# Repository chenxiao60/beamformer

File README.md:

beamformer
==============

Source files for senior tech project

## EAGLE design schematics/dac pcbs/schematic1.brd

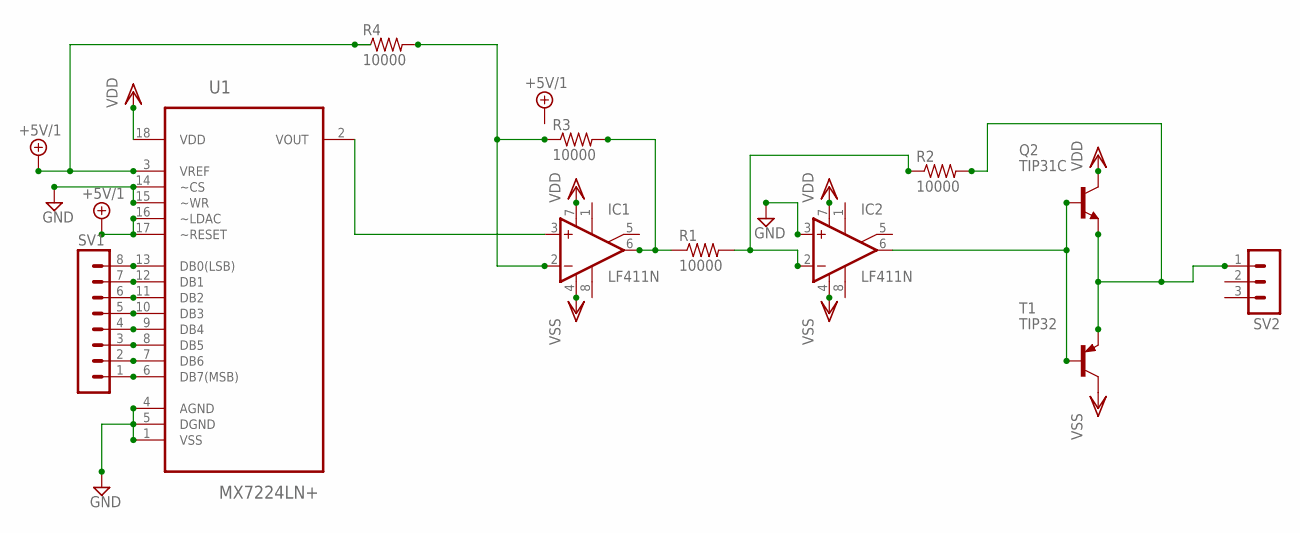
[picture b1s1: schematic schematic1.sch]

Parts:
IC1, IC2: LF411N; DIL08
Q2: TIP31C; TO220
R1, R2, R3, R4: 10000; 0204/7
SV1: MA08-1W
SV2: MA03-1
T1: TIP32; TO220
U1: MX7224LN+; DIP254P762X457-18

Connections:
+5V/1: R4.1, U1.3 (VREF), U1.16 (~LDAC), U1.17 (~RESET)
GND: IC2.3 (+IN), U1.1 (VSS), U1.4 (AGND), U1.5 (DGND), U1.14 (~CS), U1.15 (~WR)
unnamed: IC1.6 (OUT), R1.1, R3.2
unnamed: IC2.2 (-IN), R1.2, R2.1
unnamed: IC2.6 (OUT), Q2.1 (B), T1.1 (B)
unnamed: IC1.3 (+IN), U1.2 (VOUT)
unnamed: IC1.2 (-IN), R3.1, R4.2
unnamed: SV1.1, U1.6 (DB7(MSB))
unnamed: SV1.2, U1.7 (DB6)
unnamed: SV1.3, U1.8 (DB5)
unnamed: SV1.4, U1.9 (DB4)
unnamed: SV1.5, U1.10 (DB3)
unnamed: SV1.6, U1.11 (DB2)
unnamed: SV1.7, U1.12 (DB1)
unnamed: SV1.8, U1.13 (DB0(LSB))
O0: Q2.3 (E), R2.2, SV2.1, T1.3 (E)
VDD: IC1.7 (V+), IC2.7 (V+), Q2.2 (C), U1.18 (VDD)
VSS: IC1.4 (V-), IC2.4 (V-), T1.2 (C)

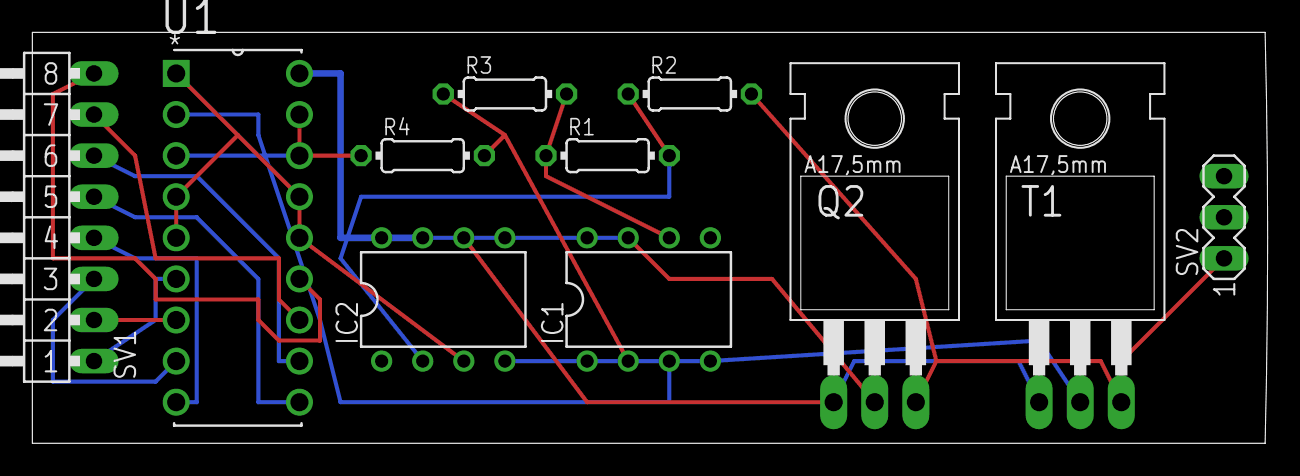
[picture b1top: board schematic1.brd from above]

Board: 2 copper layers, 76.4 x 25.4 mm, 11 parts (0 on the bottom side), 18 nets.

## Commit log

2013-12-10 initial version
2013-12-10 cleaned up naming
2013-12-10 fixed testbench
2013-12-10 working simulation
2013-12-10 new idea for timing
2013-12-10 channel select timing working
2013-12-10 ds_store changed
2013-12-12 initial dac timing fix
2013-12-18 edited ucf file
2014-01-07 configured testbech
2014-01-07 caught bug in input method
2014-01-07 testbench edits
2014-01-09 ldac timing fix
2014-01-10 ldac refix
2014-01-16 fixed overflow issues
2014-02-12 used combinatorial logic
2014-02-26 changed delays
2014-02-26 changed comment
2014-02-26 new method for processing
2014-02-26 fixed counter labeling
2014-02-27 changed simulation method
2014-02-27 cleared data bus buffers on each us clock
2014-02-27 new method to clear registers
2014-02-27 added high impedence output
2014-02-27 deleted high impedence output
2014-02-27 changed to quiessent point output
2014-02-27 changed sample period
2014-02-27 edited out clearing registers
2014-03-07 sample period update
2014-03-10 initial farfield commit
2014-03-10 wrote far-field delays
2014-03-11 loading registers fix
2014-03-11 fixed sample_edges
2014-03-11 fixed clock issues
2014-03-11 fixed clock division issue
2014-03-11 fixed counter timing
2014-03-11 far-field working
2014-03-11 far-field synthesizes
2014-03-12 all outputs working
2014-03-13 changed sample timing
2014-03-13 updated pin names & changed sampling method
2014-03-14 new output method
2014-03-14 fixed sample_period sensitivity list issue
2014-03-14 synchronous resets
2014-03-14 updated delays to generics
2014-03-14 new counter method
2014-03-14 fixed sample updating
2014-03-14 nearfield working
2014-03-17 combined into one repo
2014-03-17 cleaning repo
2014-03-17 added website
2014-03-17 edited readme
2014-03-17 cleaned up repo
2014-03-17 preparing for gh-pages
2014-03-17 moved to gh-pages
2014-03-17 fixed website error
2014-03-17 ds store changed
2014-03-26 uncommented delay alg
2014-03-26 changed libraries
2014-03-26 switched type of distance
2014-03-26 added unsigned library
2014-03-26 uncommented delay methods
2014-03-26 added in anti-sound method
2014-04-09 pipelined squareroot
2014-04-09 fixed multiply by 0.5
2014-04-09 distance to delay simulates
2014-04-11 scaled distance to delay method by 10^3
2014-04-25 adding accuracy
2014-04-25 changed system photo
2014-04-25 updated to 3.1.1
2014-04-25 added 3.1.1 files
2014-04-25 edited description
2014-04-25 responsive navbar not working
2014-04-30 method working, need fixed
2014-04-30 deleted <CR>
2014-04-30 moved delay calculation to own file
2014-04-30 converted signals to ufixed
2014-04-30 converting to ufixed
2014-04-30 tried adding id
2014-04-30 ready to test fixed num
2014-04-30 updated index
2014-05-01 edited navbar
2014-05-01 fixed navbar
2014-05-01 cleaning code
2014-05-02 added fixed library
2014-05-02 adding fixed num package
2014-05-16 working in Firefox
2014-05-16 working in Safari and Chrome
2015-01-17 updated header
2015-01-17 added photos section
2015-06-06 ds store
2015-06-06 added schematics and papers
2015-06-06 updated schematics
